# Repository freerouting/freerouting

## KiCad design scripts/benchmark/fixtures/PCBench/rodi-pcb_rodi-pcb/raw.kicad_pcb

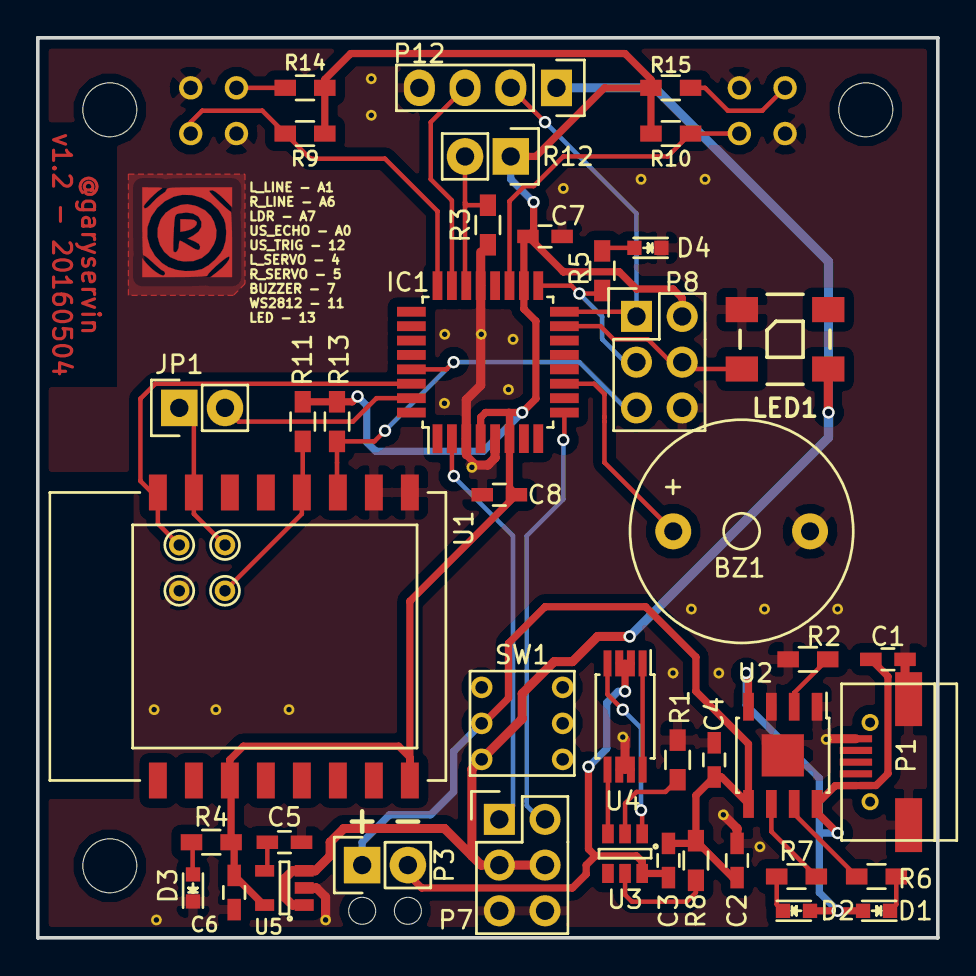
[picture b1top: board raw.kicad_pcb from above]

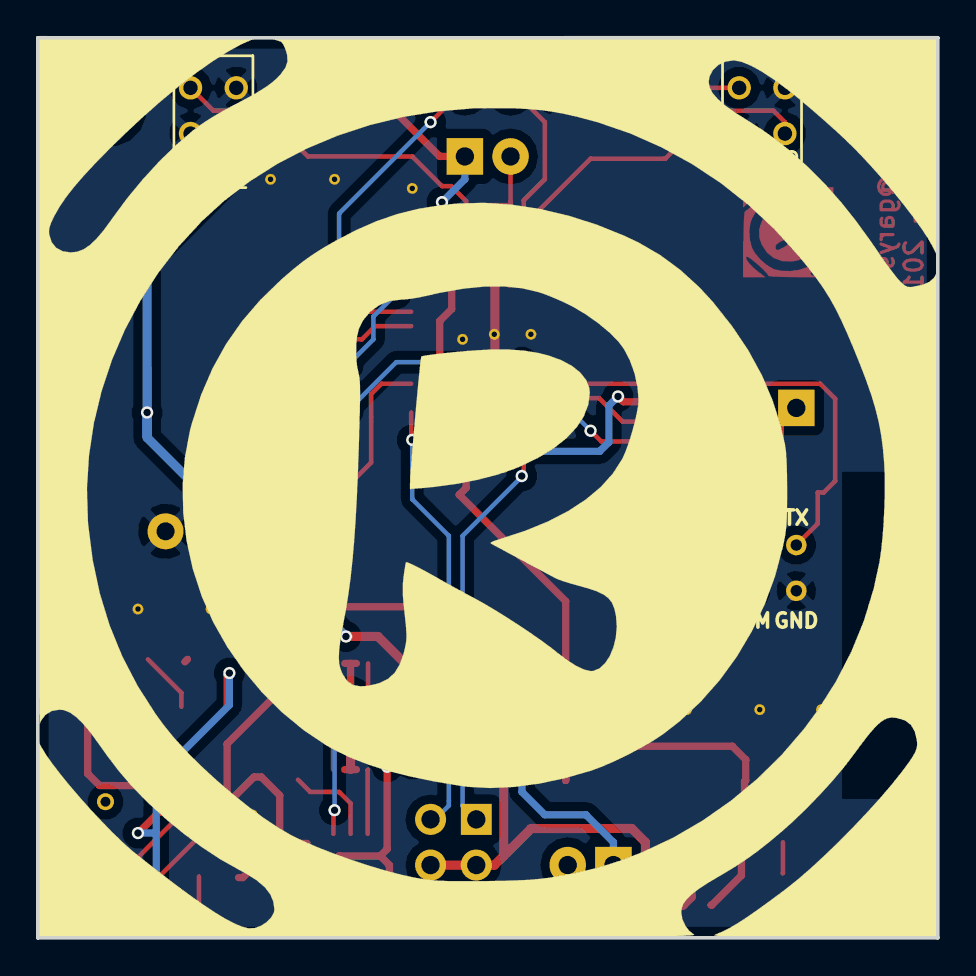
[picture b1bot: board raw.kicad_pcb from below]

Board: 2 copper layers, 50.0 x 50.0 mm, 48 parts (2 on the bottom side), 36 nets.

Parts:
BZ1: BUZZER; Buzzer_12x9.5RM7.6
C1, C2: 10u; C_0603_HandSoldering
C3, C5, C7, C8: 100n; C_0603_HandSoldering
C4, C6: 1u; C_0603_HandSoldering
D1: CHRG; LED-0603
D2: STDBY; LED-0603
D3: PWR; LED-0603
D4: L13; LED-0603
IC1: ATMEGA328P-A; TQFP-32_7x7mm_Pitch0.8mm
JP1: ESP_RX; Pin_Header_Straight_1x02
LED1: WS2812B
P1: USB_OTG; USB_Micro-B
P2, P4, P5, P6: TST; PINTST
P3: BATT; Pin_Header_Straight_1x02
P7: CONN_02X03; Pin_Header_Straight_2x03
P8: ICSP; Pin_Header_Straight_2x03
P12: US1; Pin_Header_Straight_1x04
QRD1: L_LINE; QRD1114
QRD2: R_LINE; QRD1114
R1, R3, R4, R5, R6, R7: 1K; R_0603_HandSoldering
R2: 1K2; R_0603_HandSoldering
R8: 100; R_0603_HandSoldering
R9, R10, R11, R13: 10K; R_0603_HandSoldering
R12: LDR; Pin_Header_Straight_1x02
R14, R15: 220; R_0603_HandSoldering
SW1: ON_OFF; SW_DPDT_5.8
U1: ESP8266-07; ESP8266_ESP-07
U2: TP4056; SOIC-8-1EP_3.9x4.9mm_Pitch1.27mm
U3: DW01-G; SOT-23-6
U4: FS8205; TSSOP-8_4.4x3mm_Pitch0.65mm
U5: SGM2019; SOT-23-5

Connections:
+3V3: C6.1, C7.1, C8.1, IC1.4, IC1.6, IC1.18, P8.2, R4.1, R9.2, R10.2, R11.1, R12.1, R13.1, R14.1, R15.1, U1.11, U1.16, U5.5
+5V: C1.1, D1.2, D2.2, P1.1, U2.4, U2.8
+BATT: C2.1, C3.1, C4.1, P3.1, R8.1, SW1.5, U2.5
BUZZER: BZ1.1, IC1.11
ECHO_US1: IC1.23, P12.3
GND: BZ1.2, C1.2, C2.2, C4.2, C5.2, C6.2, C7.2, C8.2, D3.1, D4.1, IC1.3, IC1.5, IC1.21, LED1.3, P1.5, P1.6, P6.1, P7.5, P7.6, P8.6, P12.4, QRD1.E, QRD1.K, QRD2.E, QRD2.K, R1.2, R2.2, R3.2, U1.1, U1.2, U2.1, U2.3, U2.9, U4.6, U4.7, U5.2
GNDA: C3.2, P3.2, U3.6, U4.2, U4.3
LDR_SENSOR: IC1.22, R3.1, R12.2
L_LINE: IC1.24, QRD1.C, R9.1
L_SERVO: IC1.2, P7.1
MISO: IC1.16, P8.1, P12.2
MOSI: IC1.15, LED1.4, P8.4
unnamed: C5.1, U5.4
unnamed: D1.1, R6.1
unnamed: D2.1, R7.1
unnamed: D3.2, R4.2
unnamed: D4.2, R5.2
unnamed: QRD1.A, R14.2
unnamed: QRD2.A, R15.2
unnamed: R1.1, U3.2
unnamed: R2.1, U2.2
unnamed: R6.2, U2.7
unnamed: R7.2, U2.6
unnamed: R8.2, U3.5
unnamed: U4.1, U4.8
OC: U3.3, U4.5
OD: U3.1, U4.4
PGM_ESP: P2.1, R11.2, U1.4
RESET: IC1.29, P8.5, R13.2, U1.3
RXD: IC1.30, P5.1, U1.8
R_LINE: IC1.19, QRD2.C, R10.1
R_SERVO: IC1.9, P7.2
SCK: IC1.17, P8.3, R5.1
TXD: IC1.31, JP1.2
URXD_ESP: JP1.1, P4.1, U1.7
VDD: LED1.1, P7.3, P7.4, P12.1, SW1.6, U5.1, U5.3

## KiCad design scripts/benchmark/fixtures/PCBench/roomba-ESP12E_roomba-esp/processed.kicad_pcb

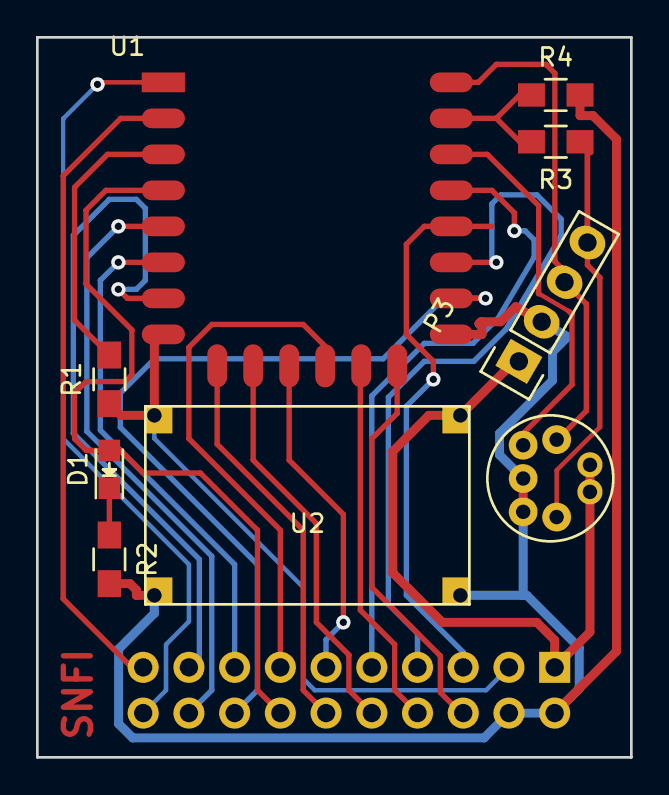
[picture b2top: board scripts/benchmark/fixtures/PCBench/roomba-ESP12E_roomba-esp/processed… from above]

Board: 2 copper layers, 33.0 x 40.0 mm, 10 parts (1 on the bottom side), 25 nets.

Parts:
D1: LED; LED-0805
P1: CONN_01X07; mini_DIN_7
P2: CONN_02X10; Socket_Strip_Angled_2x10
P3: CONN_01X04; Socket_Strip_Straight_1x04
R1, R4: 10K; R_0805_HandSoldering
R2: 1K; R_0805_HandSoldering
R3: 5K; R_0805_HandSoldering
U1: ESP-12E
U2: LM2596_module

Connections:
/ADC: P2.19, U1.2
/CS0: P2.12, U1.9
/DD: P1.5, U1.20
/GPIO0: P2.5, U1.18
/GPIO2: P2.7, U1.17
/GPIO5: P2.9, U1.19
/GPIO9: P2.11, U1.11
/GPIO10: P2.13, U1.12
/GPIO12: P2.15, U1.6
/GPIO13: P2.17, U1.7
/GPIO14: P2.18, U1.5
/GPIO15: P2.16, U1.16
/GPIO16: D1.2, P2.14, U1.4
/MISO: P2.10, U1.10
/MOSI: P2.8, U1.13
/RESET: P2.20, U1.1
/RX: R3.2, R4.1, U1.21
/RX_R: P1.3, P3.3, U1.22
/SCK: P2.6, U1.14
/TX_R: P1.4, P3.4, R3.1
/VBat: P1.1, P1.2, P2.1, P3.1, U2.4
GND: P1.6, P1.7, P2.2, P2.4, P3.2, R2.2, R4.2, U1.15, U2.2, U2.3
unnamed: D1.1, R2.1
unnamed: R1.2, U1.3
VCC: P2.3, R1.1, U1.8, U2.1

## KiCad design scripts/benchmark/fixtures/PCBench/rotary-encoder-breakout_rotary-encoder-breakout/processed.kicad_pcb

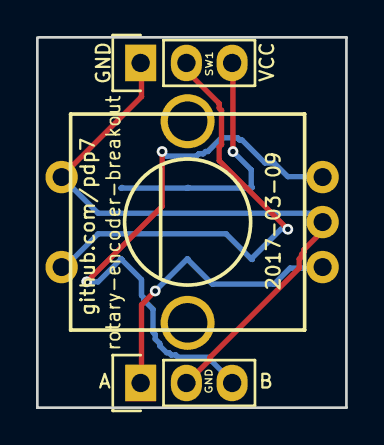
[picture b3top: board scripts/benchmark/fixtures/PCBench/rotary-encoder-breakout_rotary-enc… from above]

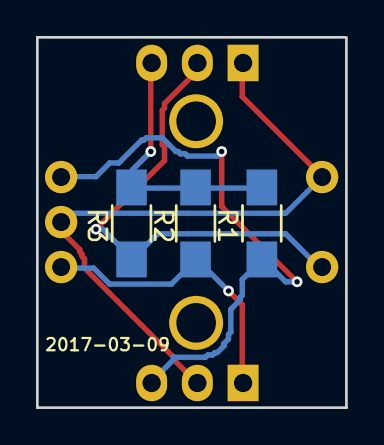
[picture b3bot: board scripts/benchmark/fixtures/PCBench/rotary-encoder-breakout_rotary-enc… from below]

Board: 2 copper layers, 17.2 x 20.6 mm, 6 parts (3 on the bottom side), 5 nets.

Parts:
P1, P5: CONN_01X03; Pin_Header_Straight_1x03
R1, R2, R3: R; R_1206_HandSoldering
ROT1: ROTARY-ENCODER; SF-ROTARY-ENCODER

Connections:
/VCC: P1.3, R1.2, R2.2, R3.2
unnamed: P1.1, P5.2, ROT1.3, ROT1.5
unnamed: P1.2, R3.1, ROT1.1
unnamed: P5.1, R2.1, ROT1.2
unnamed: P5.3, R1.1, ROT1.4
